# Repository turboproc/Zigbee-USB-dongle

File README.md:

# Introduction

USB dongle to host the EBYTE C1352P Zigbee module. Main features:
- E79-400DM2005S Zigbee module
- CH340E USB controller
- 2 on board leds
- button to open bootloader backdoor
- CJTAG interface through 6 pin header 
 
The 6 pin connector matches the [Zigbee dongle adapter] (https://github.com/turboproc/Zigbee-dongle-adapter) which allows easy connection to the TI CC-DEVPACK-DEBUG board.

**WARNING: this is work in progress. Designs still need to be validaded on first prototypes.**

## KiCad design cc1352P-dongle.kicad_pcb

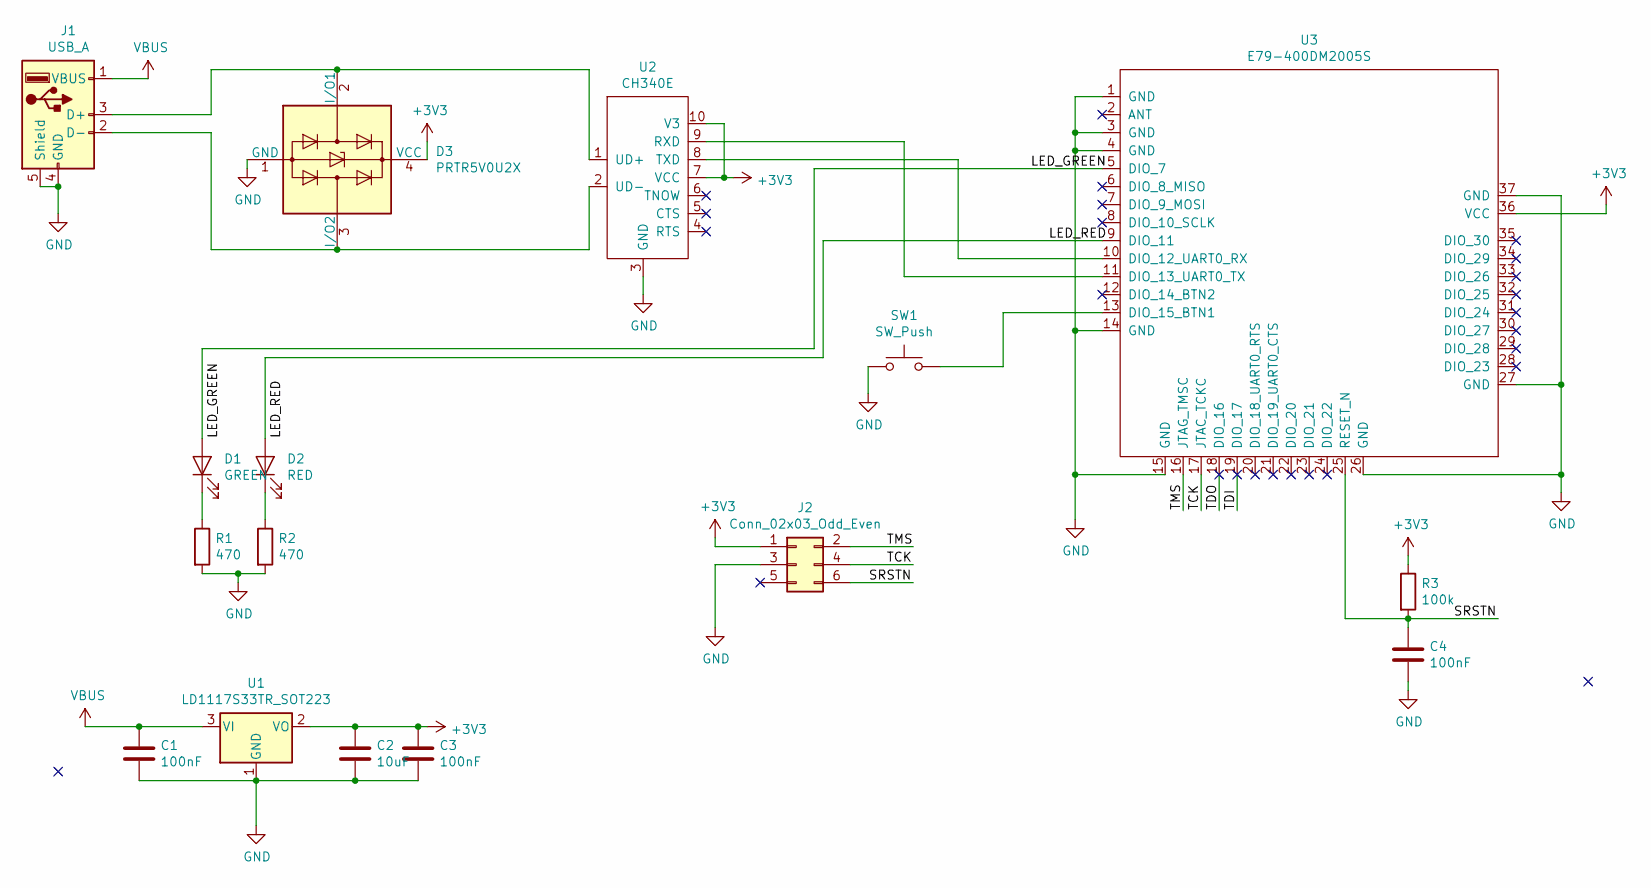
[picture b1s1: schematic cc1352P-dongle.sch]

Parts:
C1, C3, C4: 100nF; C_0603_1608Metric_Pad1.05x0.95mm_HandSolder
C2: 10uF; C_0603_1608Metric_Pad1.05x0.95mm_HandSolder
D1: GREEN; LED_0603_1608Metric_Pad1.05x0.95mm_HandSolder
D2: RED; LED_0603_1608Metric_Pad1.05x0.95mm_HandSolder
D3: PRTR5V0U2X; SOT-143
J1: USB_A
J2: Conn_02x03_Odd_Even; PinHeader_2x03_P2.54mm_Vertical
R1, R2: 470; R_0603_1608Metric_Pad1.05x0.95mm_HandSolder
R3: 100k; R_0603_1608Metric_Pad1.05x0.95mm_HandSolder
SW1: SW_Push; SW_SPST_B3U-3000P
U1: LD1117S33TR_SOT223; SOT-223-3_TabPin2
U2: CH340E; MSOP-10_3x3mm_P0.5mm
U3: E79-400DM2005S

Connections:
+3V3: C2.1, C3.1, D3.4 (VCC), J2.1, R3.1, U1.2 (VO), U2.7 (VCC), U2.10 (V3), U3.36 (VCC)
/LED_GREEN: D1.2 (A), U3.5 (DIO_7)
/LED_RED: D2.2 (A), U3.9 (DIO_11)
/SRSTN: C4.1, J2.6, R3.2, U3.25 (RESET_N)
/TCK: J2.4, U3.17 (JTAC_TCKC)
/TDI: U3.19 (DIO_17)
/TDO: U3.18 (DIO_16)
/TMS: J2.2, U3.16 (JTAG_TMSC)
GND: C1.2, C2.2, C3.2, C4.2, D3.1 (GND), J1.4 (GND), J1.5 (Shield), J2.3, R1.2, R2.2, SW1.1, U1.1 (GND), U2.3 (GND), U3.1 (GND), U3.3 (GND), U3.4 (GND), U3.14 (GND), U3.15 (GND), U3.26 (GND), U3.27 (GND), U3.37 (GND)
unnamed: D1.1 (K), R1.1
unnamed: D2.1 (K), R2.1
unnamed: D3.2 (I/O1), J1.3 (D+), U2.1 (UD+)
unnamed: D3.3 (I/O2), J1.2 (D-), U2.2 (UD-)
unnamed: SW1.2, U3.13 (DIO_15_BTN1)
unnamed: U2.8 (TXD), U3.10 (DIO_12_UART0_RX)
unnamed: U2.9 (RXD), U3.11 (DIO_13_UART0_TX)
VBUS: C1.1, J1.1 (VBUS), U1.3 (VI)

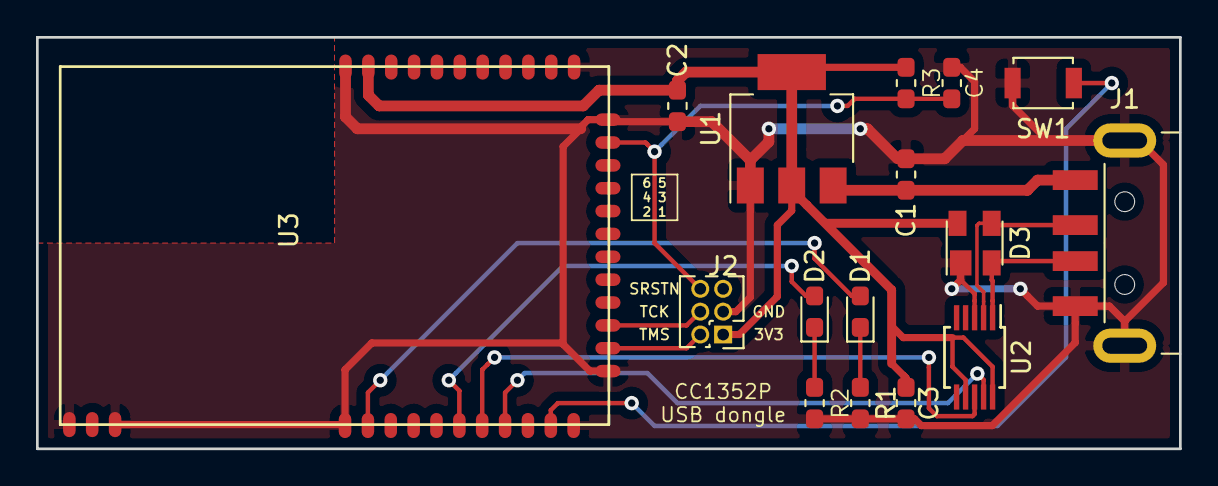
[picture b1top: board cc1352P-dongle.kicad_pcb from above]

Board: 2 copper layers, 63.5 x 22.9 mm, 16 parts (0 on the bottom side), 15 nets.
